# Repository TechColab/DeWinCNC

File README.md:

DeWinCNC brings the benefits of the RAMPS eco-system to machines which originated with WinCNC.

Compared with WinCNC:
WinCNC software uses a proprietory daughter card on a full-size PCI I/O card which needs a Windows desktop PC.

This shield + an Arduino MEGA 2560 + Marlin firmware enables you to use a laptop of any OS you like, 
with a choice of controller/loader apps.  Or no computer at all - just load files from an SD-card!

You can use entirely open source software with no license or on-going maintenance costs.
Or you can chose somehting like LightBurn which has a great camera feature at a great price.

In common with WinCNC:
Includes the same DB37 plug for direct connection to your existing machne's breakout board.

Compared with RAMPS:
Uses common industrial off-board stepper driver modules so you can scale to any power your mechine needs.

Has a 1-Wire interface so you can use as many digital temperature sensors as you like.

Has 4 on-board isolated SolidState Relays for switching machine power, GasAssist, VacuumPump etc.

Can take power entirely from the USB host, or from a common industrial 24Vdc supply.

Limit switch inputs have convenient screw-terminal connectors.

In common with RAMPS:
Limit switch headers, I2C & reset botton.
Keeps the Aux-1,2,3,4 ports for Servos, SD-card, LCD contoler etc. within the same footprint.

Additional functionality:
Could be plugged into the WinCNC controller to replace the CNC machine's breakout board.
Could be used with the WinCNC controller to monitor/simulate most signals.
Can be used as a general purpose breakout shield with 4 SSRs & 23 I/O lines (inc 10 analog).

ToDo:
Most PCB manufacturers will want a bigger gap between main & break-off boards.  And perforation holes.

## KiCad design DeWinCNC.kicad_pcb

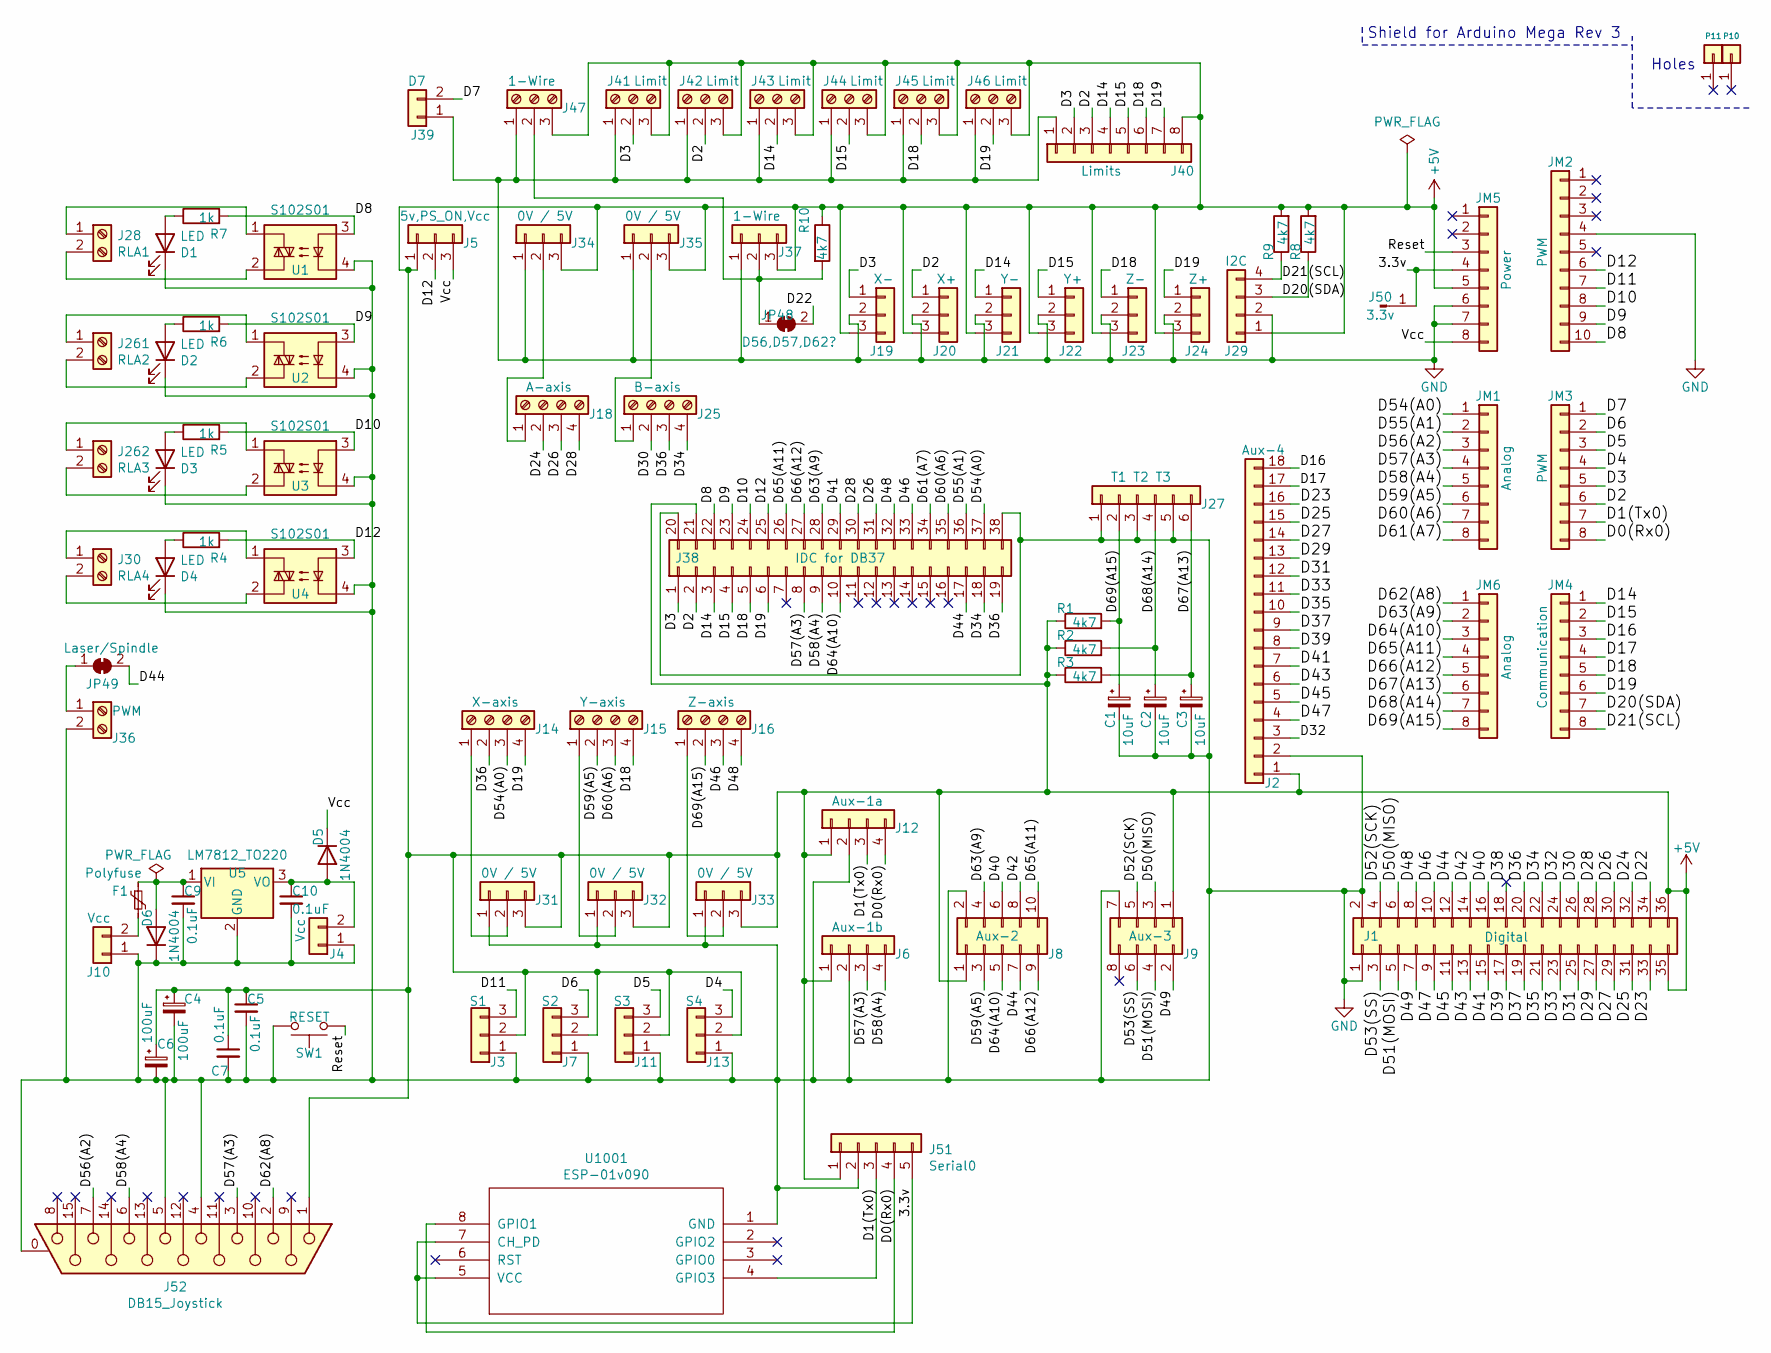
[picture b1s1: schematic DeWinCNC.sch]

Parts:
C1, C2, C3: 10uF
C4, C6: 100uF
C5, C7, C9, C10: 0.1uF
D1, D2, D3, D4: LED
D5, D6: 1N4004; D_DO-41_SOD81_P10.16mm_Horizontal
F1: Polyfuse
J1: Digital; Socket_Strip_Arduino_2x18
J2: Aux-4
J3: S1
J4, J10: Vcc
J5: 5v,PS_ON,Vcc
J6: Aux-1b
J7: S2
J8: Aux-2
J9: Aux-3
J11: S3
J12: Aux-1a
J13: S4
J14: X-axis
J15: Y-axis
J16: Z-axis
J18: A-axis
J19: X-
J20: X+
J21: Y-
J22: Y+
J23: Z-
J24: Z+
J25: B-axis
J27: T1 T2 T3
J28: RLA1
J29: I2C
J30: RLA4
J31, J32, J33, J34, J35: 0V / 5V
J36: PWM
J37, J47: 1-Wire
J38: IDC for DB37
J39: D7
J40: Limits; Socket_Strip_Arduino_1x08
J41, J42, J43, J44, J45, J46: Limit
J50: 3.3v
J51: Serial0
J52: DB15_Joystick
J261: RLA2
J262: RLA3
JM1, JM6: Analog; Socket_Strip_Arduino_1x08
JM2: PWM; Socket_Strip_Arduino_1x10
JM3: PWM; Socket_Strip_Arduino_1x08
JM4: Communication; Socket_Strip_Arduino_1x08
JM5: Power; Socket_Strip_Arduino_1x08
JP48: D56,D57,D62?
JP49: Laser/Spindle
P10, P11: CONN_01X01; Arduino_1pin
R1, R2, R3, R8, R9, R10: 4k7
R4, R5, R6, R7: 1k
SW1: RESET
U1, U2, U3, U4: S102S01; SIP4_Sharp-SSR_P7.62mm_Straight
U5: LM7812_TO220; TO-220-3_Vertical
U1001: ESP-01v090; PinSocket_2x04_P2.54mm_Vertical

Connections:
+5V: C4.1, C5.1, C6.1, C7.1, J1.35, J1.36, J2.1, J3.2, J5.1, J6.1, J7.2, J8.1, J9.1, J11.2, J12.1, J13.2, J19.3, J20.3, J21.3, J22.3, J23.3, J24.3, J29.1, J31.3, J32.3, J33.3, J34.3, J35.3, J37.3, J38.21, J40.8, J41.3, J42.3, J43.3, J44.3, J45.3, J46.3, J47.3, J51.1, J52.1, JM5.5, R1.1, R2.1, R3.1, R8.2, R9.2, R10.1
/3.3v: J50.1, J51.5, JM5.4, U1001.5 (VCC), U1001.7 (CH_PD); also elsewhere on the board
/D0(Rx0): J12.4, J51.4, JM3.8, U1001.8 (GPIO1); also elsewhere on the board
/D1(Tx0): J12.3, J51.3, JM3.7, U1001.4 (GPIO3); also elsewhere on the board
/D2: J20.1, J38.2, J40.3, J42.2, JM3.6
/D3: J19.1, J38.1, J40.2, J41.2, JM3.5
/D4: J13.3, JM3.4
/D5: J11.3, JM3.3
/D6: J7.3, JM3.2
/D7: J39.2, JM3.1
/D8: J38.22, JM2.10, R7.2, U1.3
/D9: J38.23, JM2.9, R6.2, U2.3
/D10: J38.24, JM2.8, R5.2, U3.3
/D11: J3.3, JM2.7
/D12: J5.2, J38.25, JM2.6, R4.2, U4.3
/D14: J21.1, J38.3, J40.4, J43.2, JM4.1
/D15: J22.1, J38.4, J40.5, J44.2, JM4.2
/D16: J2.18, JM4.3
/D17: J2.17, JM4.4
/D18: J15.4, J23.1, J38.5, J40.6, J45.2, JM4.5
/D19: J14.4, J24.1, J38.6, J40.7, J46.2, JM4.6
/D20(SDA): J29.3, JM4.7, R8.1
/D21(SCL): J29.4, JM4.8, R9.1
/D22: J1.34, JP48.2 (B)
/D23: J1.33, J2.16
/D24: J1.32, J18.2
/D25: J1.31, J2.15
/D26: J1.30, J18.3, J38.31
/D27: J1.29, J2.14
/D28: J1.28, J18.4, J38.30
/D29: J1.27, J2.13
/D30: J1.26, J25.2
/D31: J1.25, J2.12
/D32: J1.24, J2.3
/D33: J1.23, J2.11
/D34: J1.22, J25.4, J38.18
/D35: J1.21, J2.10
/D36: J1.20, J14.2, J25.3, J38.19
/D37: J1.19, J2.9
/D38: J1.18
/D39: J1.17, J2.8
/D40: J1.16, J8.6
/D41: J1.15, J2.7, J38.29
/D42: J1.14, J8.8
/D43: J1.13, J2.6
/D44: J1.12, J8.7, J38.17, JP49.2 (B)
/D45: J1.11, J2.5
/D46: J1.10, J16.3, J38.33
/D47: J1.9, J2.4
/D48: J1.8, J16.4, J38.32
/D49: J1.7, J9.2
/D50(MISO): J1.6, J9.3
/D51(MOSI): J1.5, J9.4
/D52(SCK): J1.4, J9.5
/D53(SS): J1.3, J9.6
/D54(A0): J14.3, J38.37, JM1.1
/D55(A1): J38.36, JM1.2
/D56(A2): J52.7, JM1.3
/D57(A3): J6.3, J38.8, J52.3, JM1.4
/D58(A4): J6.4, J38.9, J52.6, JM1.5
/D59(A5): J8.3, J15.2, JM1.6
/D60(A6): J15.3, J38.35, JM1.7
/D61(A7): J38.34, JM1.8
/D62(A8): J52.2, JM6.1
/D63(A9): J8.4, J38.28, JM6.2
/D64(A10): J8.5, J38.10, JM6.3
/D65(A11): J8.10, J38.26, JM6.4
/D66(A12): J8.9, J38.27, JM6.5
/D67(A13): C3.1, J27.6, JM6.6, R3.2
/D68(A14): C2.1, J27.4, JM6.7, R2.2
/D69(A15): C1.1, J16.2, J27.2, JM6.8, R1.2
/Reset: JM5.3, SW1.1; also elsewhere on the board
/Vcc: D5.1 (K), J5.3, JM5.8
GND: C1.2, C2.2, C3.2, C4.2, C5.2, C6.2, C7.2, C9.2, C10.2, D1.1 (K), D2.1 (K), D3.1 (K), D4.1 (K), D6.1 (K), J1.1, J1.2, J2.2, J3.1, J4.1, J6.2, J7.1, J8.2, J9.7, J10.1, J11.1, J12.2, J13.1, J19.2, J20.2, J21.2, J22.2, J23.2, J24.2, J27.1, J27.3, J27.5, J29.2, J31.1, J32.1, J33.1, J34.1, J35.1, J36.2, J37.1, J38.20, J38.38, J39.1, J40.1, J41.1, J42.1, J43.1, J44.1, J45.1, J46.1, J47.1, J51.2, J52.0 (PAD), J52.4, J52.5, JM2.4, JM5.6, JM5.7, SW1.2, U1.4, U2.4, U3.4, U4.4, U5.2 (GND), U1001.1 (GND); also elsewhere on the board
unnamed: C9.1, D6.2 (A), F1.1, U5.1 (VI)
unnamed: C10.1, D5.2 (A), J4.2, U5.3 (VO)
unnamed: D1.2 (A), R7.1
unnamed: D2.2 (A), R6.1
unnamed: D3.2 (A), R5.1
unnamed: D4.2 (A), R4.1
unnamed: F1.2, J10.2
unnamed: J14.1, J31.2
unnamed: J15.1, J32.2
unnamed: J16.1, J33.2
unnamed: J18.1, J34.2
unnamed: J25.1, J35.2
unnamed: J28.1, U1.1
unnamed: J28.2, U1.2
unnamed: J30.1, U4.1
unnamed: J30.2, U4.2
unnamed: J36.1, JP49.1 (A)
unnamed: J37.2, J47.2, JP48.1 (A), R10.2
unnamed: J261.1, U2.1
unnamed: J261.2, U2.2
unnamed: J262.1, U3.1
unnamed: J262.2, U3.2

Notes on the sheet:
Shield for Arduino Mega Rev 3
Holes

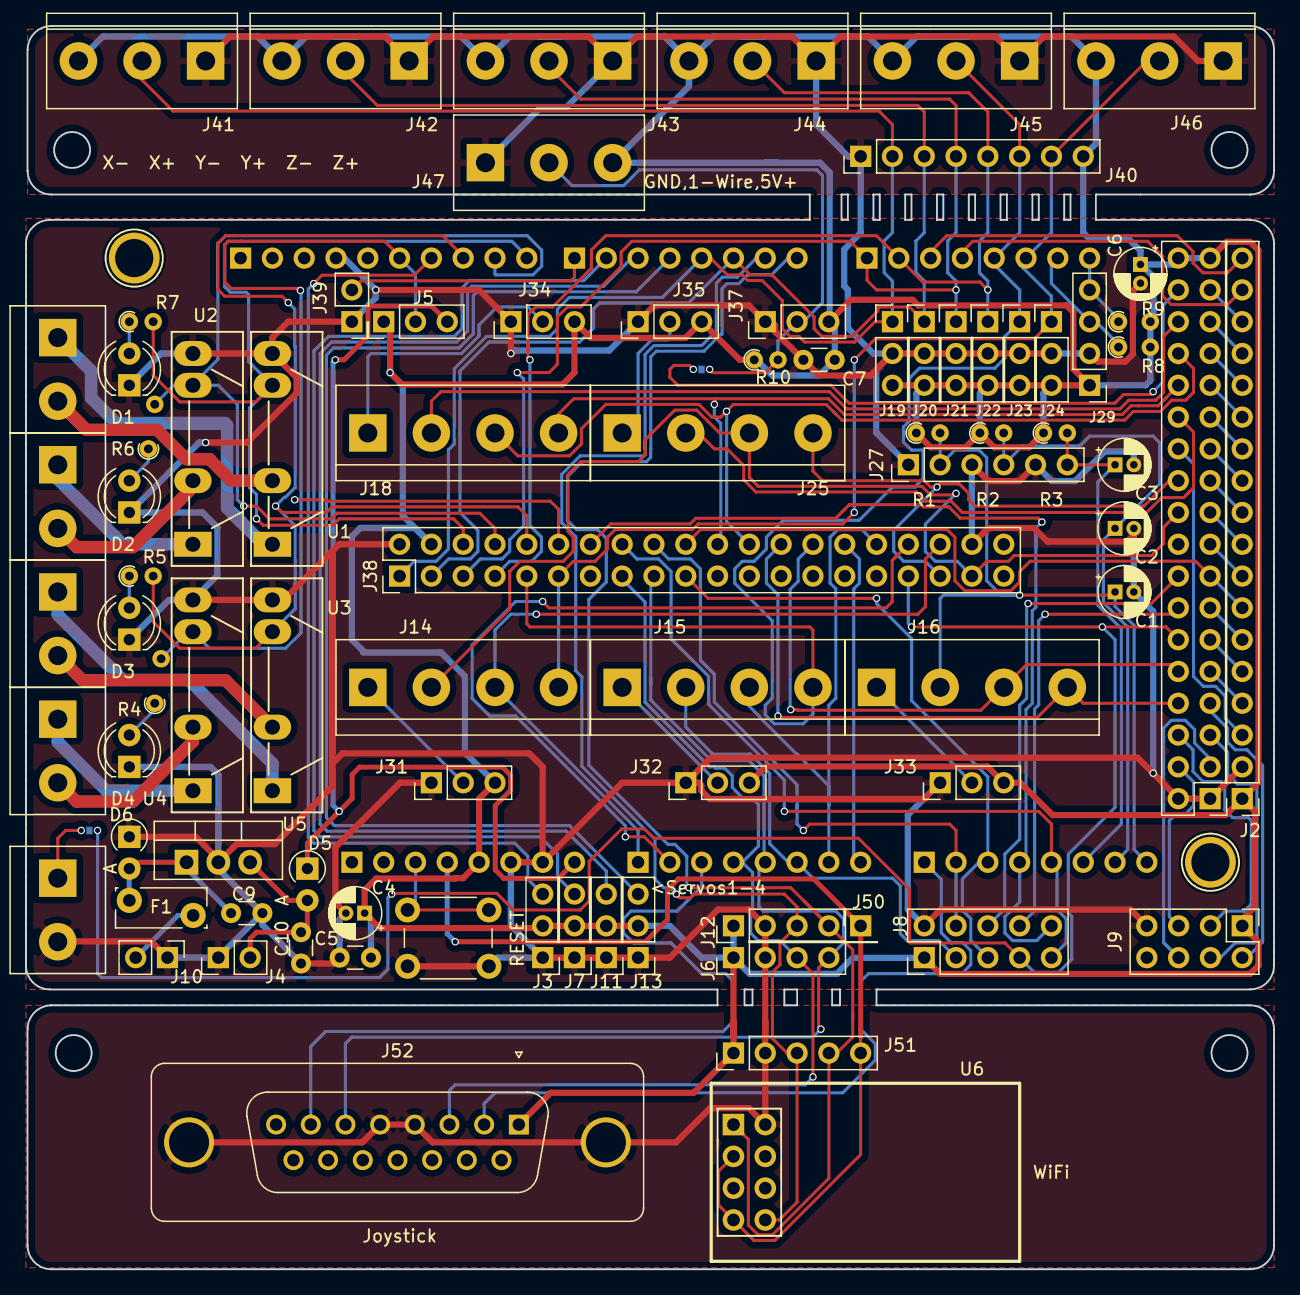
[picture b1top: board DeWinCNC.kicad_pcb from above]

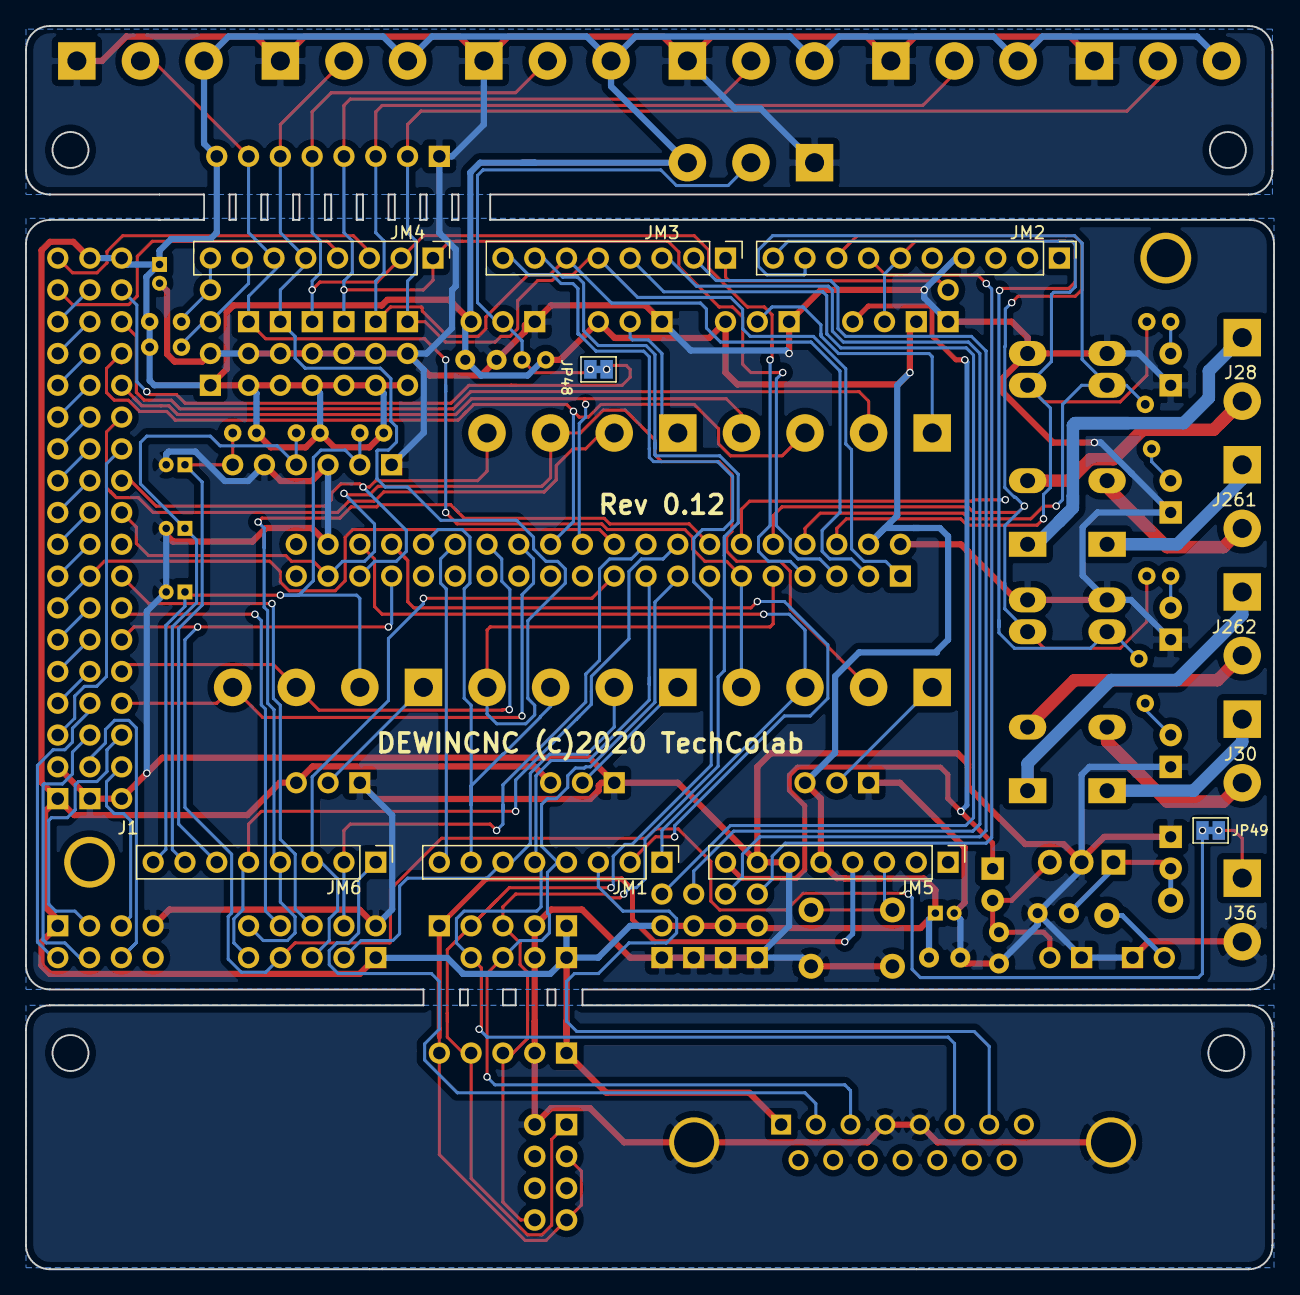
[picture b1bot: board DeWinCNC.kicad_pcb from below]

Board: 2 copper layers, 99.7 x 99.3 mm, 93 parts (9 on the bottom side), 95 nets.

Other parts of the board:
RESET: RESET; SW_PUSH_6mm_H4.3mm
U6: ESP-01v090; ESP-01

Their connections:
/3.3v: U6.3, U6.7; also elsewhere on the board
/D0(Rx0): U6.1; also elsewhere on the board
/D1(Tx0): U6.8; also elsewhere on the board
/Reset: RESET.1; also elsewhere on the board
GND: RESET.2, U6.2; also elsewhere on the board

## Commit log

2020-10-31 Initial upload
2021-04-01 Update ESP pinout, round edges more.

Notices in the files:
DeWinCNC.kicad_pcb:
DEWINCNC (c)2020 TechColab
